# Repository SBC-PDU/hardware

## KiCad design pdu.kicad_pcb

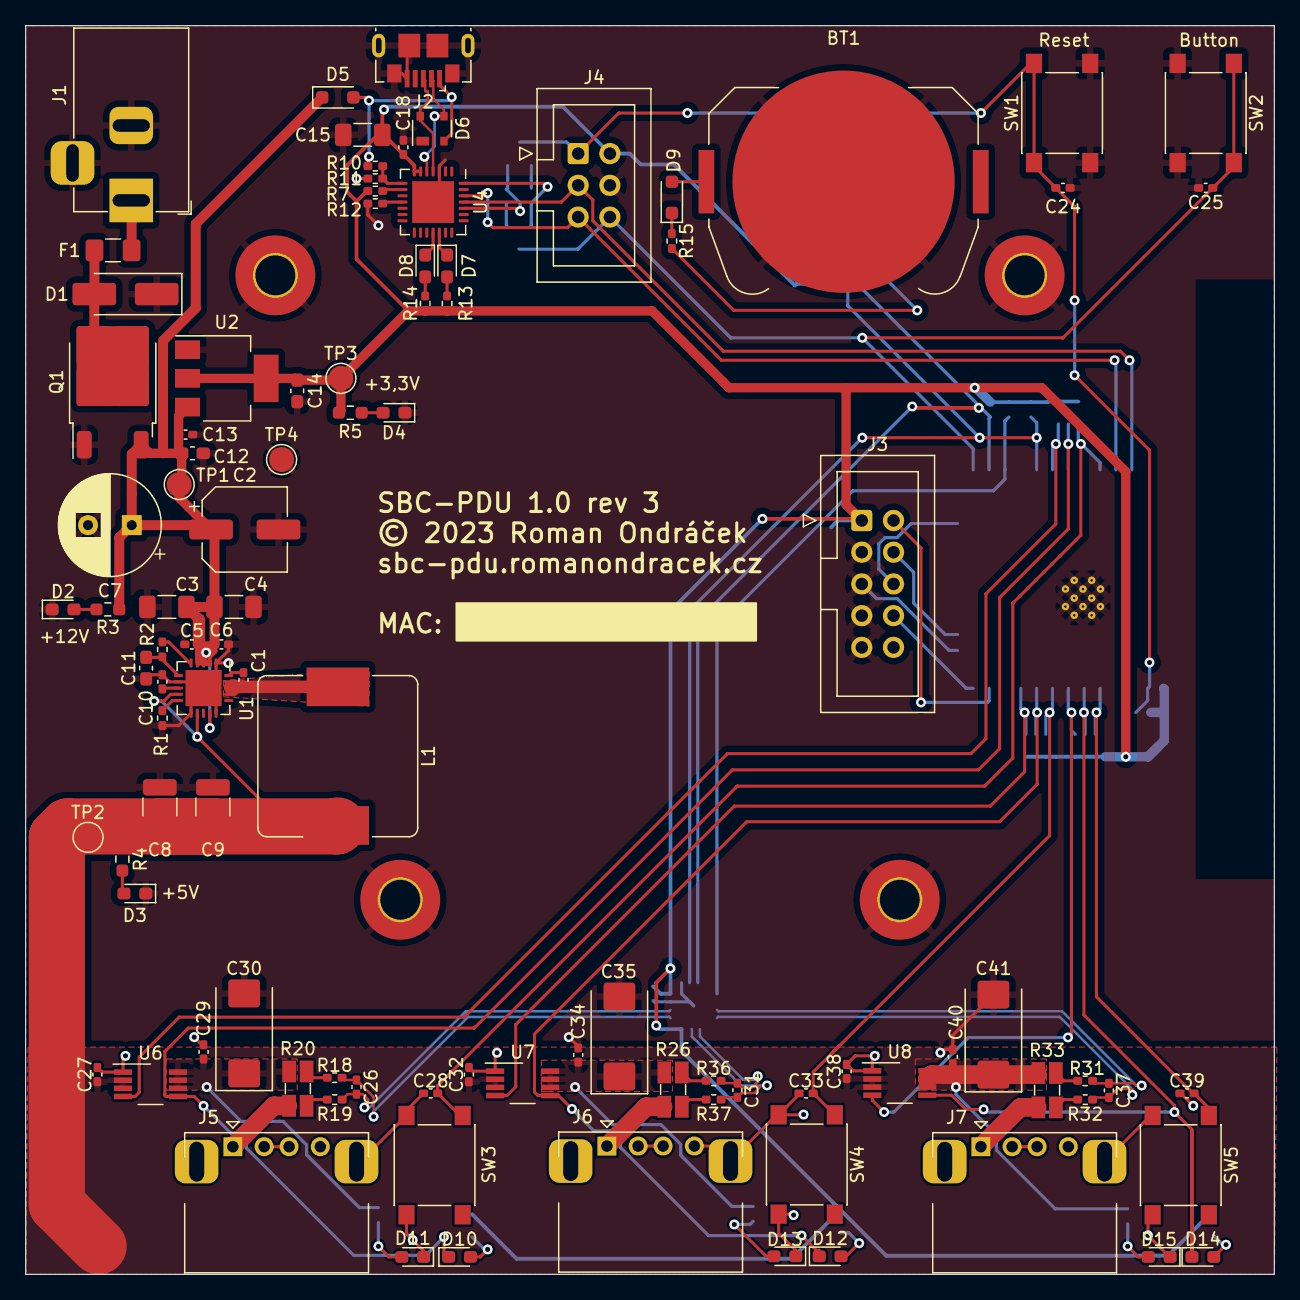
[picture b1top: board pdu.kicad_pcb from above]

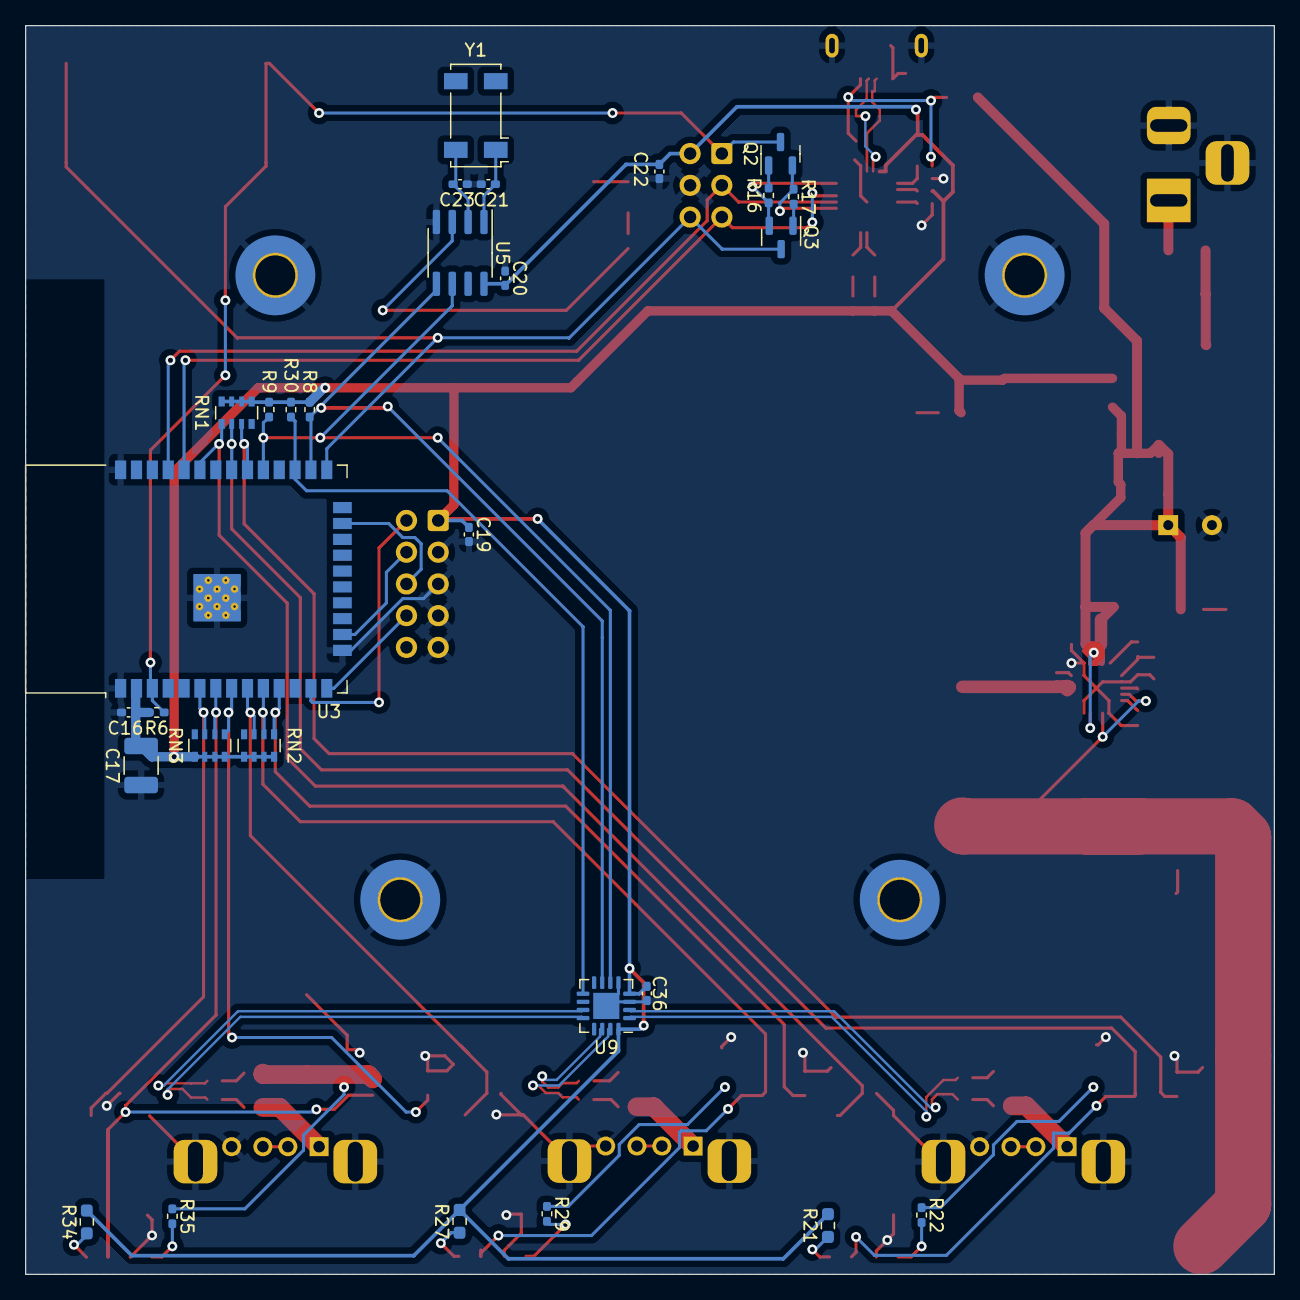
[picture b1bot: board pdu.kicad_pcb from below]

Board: 2 copper layers, 100.0 x 100.0 mm, 128 parts (29 on the bottom side), 81 nets.

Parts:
BT1: CR2032; BatteryHolder_Keystone_3034_1x20mm
C1, C13, C16, C18, C19, C20, C22, C24, C25, C27, C28, C29, C31, C32, C33, C34, C36, C37, C38, C39, C40: 100n; C_0402_1005Metric_Pad0.74x0.62mm_HandSolder
C2: 47u; CP_Elec_6.3x5.8
C3, C4, C15: 4.7u; C_1206_3216Metric_Pad1.33x1.80mm_HandSolder
C5, C6: 150p; C_0402_1005Metric_Pad0.74x0.62mm_HandSolder
C7: 470u; CP_Radial_D8.0mm_P3.50mm
C8, C9: 47u; C_1210_3225Metric_Pad1.33x2.70mm_HandSolder
C10: 5600p; C_0402_1005Metric_Pad0.74x0.62mm_HandSolder
C11: 2.2u; C_0603_1608Metric_Pad1.08x0.95mm_HandSolder
C12: 1u; C_0603_1608Metric_Pad1.08x0.95mm_HandSolder
C14: 10u; C_0603_1608Metric_Pad1.08x0.95mm_HandSolder
C17: 22u; C_1210_3225Metric_Pad1.33x2.70mm_HandSolder
C21, C23: 6.8p; C_0402_1005Metric_Pad0.74x0.62mm_HandSolder
C26: C; C_0402_1005Metric_Pad0.74x0.62mm_HandSolder
C30, C35, C41: 150u; CP_EIA-7343-31_Kemet-D_Pad2.25x2.55mm_HandSolder
D1: SMAJ12CA; D_SMA_Handsoldering
D2, D3, D8, D11, D13, D15: Green_LED; LED_0603_1608Metric_Pad1.05x0.95mm_HandSolder
D4, D7, D10, D12, D14: Amber_LED; LED_0603_1608Metric_Pad1.05x0.95mm_HandSolder
D5: BAT760-7; D_SOD-323_HandSoldering
D6: SP0503BAHTG; SOT-143
D9: BAT54WS; D_SOD-323_HandSoldering
F1: 5A; Fuse_1206_3216Metric_Pad1.42x1.75mm_HandSolder
H1, H2, H3, H4: MountingHole_Pad; MountingHole_3.2mm_M3_Pad_TopBottom
J1: DC_Jack; BarrelJack_Horizontal
J2: USB_B_Micro; USB_Micro-B_GCT_USB3076-30-A
J3: JTAG; IDC-Header_2x05_P2.54mm_Vertical
J4: UART; IDC-Header_2x03_P2.54mm_Vertical
J5, J6, J7: USB_A; USB_A_GCT_USB1125-GF-B
L1: 8.2u; L_Bourns_SRP1245A
Q1: FDD4243; TO-252-2
Q2, Q3: BC846; SOT-23
R1: 51k; R_0402_1005Metric_Pad0.72x0.64mm_HandSolder
R2, R6, R12, R15, R16, R17, R30: 10k; R_0402_1005Metric_Pad0.72x0.64mm_HandSolder
R3, R4, R5, R21, R27, R34: 430R; R_0603_1608Metric_Pad0.98x0.95mm_HandSolder
R7, R22, R29, R35: 1k; R_0402_1005Metric_Pad0.72x0.64mm_HandSolder
R8, R9: 3k3; R_0402_1005Metric_Pad0.72x0.64mm_HandSolder
R10: 22.1k; R_0402_1005Metric_Pad0.72x0.64mm_HandSolder
R11: 47.5k; R_0402_1005Metric_Pad0.72x0.64mm_HandSolder
R13, R14: 470; R_0402_1005Metric_Pad0.72x0.64mm_HandSolder
R18, R19, R31, R32, R36, R37: 10R; R_0402_1005Metric_Pad0.72x0.64mm_HandSolder
R20, R26, R33: 50m; R_Shunt_Ohmite_LVK12
RN1, RN2, RN3: 10k; R_Array_Convex_4x0603
SW1, SW2, SW3, SW4, SW5: SW_Push; SW_Push_1P1T_NO_6x6mm_H9.5mm
TP1: +12V; TestPoint_Pad_D2.0mm
TP2: +5V; TestPoint_Pad_D2.0mm
TP3: +3V3; TestPoint_Pad_D2.0mm
TP4: GND; TestPoint_Pad_D2.0mm
U1: MAX17634BATP+; TQFN-20-1EP_4x4mm_P0.5mm_EP2.9x2.9mm
U2: TLV1117LV33DCYR; SOT-223-3_TabPin2
U3: ESP32-WROOM-32D
U4: CP2102N-Axx-xQFN28; QFN-28-1EP_5x5mm_P0.5mm_EP3.35x3.35mm
U5: MCP7940N-I/SN; SOIC-8_3.9x4.9mm_P1.27mm
U6, U7, U8: TPS2000C; VSSOP-8_3.0x3.0mm_P0.65mm
U9: INA3221; Texas_RGV_S-PVQFN-N16_EP2.1x2.1mm
Y1: 32.765k; Crystal_SMD_Abracon_ABS25-4Pin_8.0x3.8mm

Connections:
+3V3: C14.1, C15.1, C16.2, C17.2, C18.1, C19.1, C20.2, C22.1, C36.2, J3.1, J4.2, R5.1, R6.1, R7.2, R8.1, R9.1, R13.1, R14.1, R21.2, R27.2, R30.1, R34.2, RN1.5 (R4.2), RN1.6 (R3.2), RN1.7 (R2.2), RN1.8 (R1.2), RN2.5 (R4.2), RN2.6 (R3.2), RN2.7 (R2.2), RN2.8 (R1.2), RN3.5 (R4.2), RN3.6 (R3.2), RN3.7 (R2.2), RN3.8 (R1.2), TP3.1, U2.2 (VO), U3.2 (VDD), U4.6 (VDD), U4.7 (VREGIN), U5.8 (VCC), U9.4 (VS), U9.16 (VPU)
+3V3_RegIn: C2.1, C3.1, C4.1, C5.1, C6.1, C7.1, C12.1, C13.1, D5.1 (K), Q1.3 (S), R3.1, TP1.1, U1.2 (IN), U1.3 (IN), U1.4 (EN/UVLO), U1.14 (IN), U2.3 (VI)
+5V: C8.1, C9.1, C27.2, C32.2, C38.2, L1.2, R4.1, TP2.1, U1.9 (FB), U1.12 (EXTVCC), U6.2 (IN), U6.3 (IN), U7.2 (IN), U7.3 (IN), U8.2 (IN), U8.3 (IN)
/ESP32/BTN: C25.1, J4.6, Q3.3 (C), SW2.1, U3.25 (IO0)
/ESP32/CRITICAL: R30.2, U3.27 (IO16), U9.9 (CRITICAL)
/ESP32/DEBUG_RX: J4.5, U3.34 (RXD0/IO3), U4.26 (TXD)
/ESP32/DEBUG_TX: J4.3, U3.35 (TXD0/IO1), U4.25 (RXD)
/ESP32/EN: C24.1, J4.1, Q2.3 (C), R6.2, SW1.1, U3.3 (EN)
/ESP32/MTCK: J3.4, U3.16 (IO13)
/ESP32/MTDI: J3.8, U3.14 (IO12)
/ESP32/MTDO: J3.6, U3.23 (IO15)
/ESP32/MTMS: J3.2, U3.13 (IO14)
/ESP32/SBC1_BTN: C28.1, RN1.1 (R1.1), SW3.1, U3.33 (IO21)
/ESP32/SBC2_BTN: C33.1, RN2.3 (R3.1), SW4.1, U3.9 (IO33)
/ESP32/SBC3_BTN: C39.1, RN3.3 (R3.1), SW5.1, U3.6 (IO34)
/ESP32/SCL: R9.2, U3.29 (IO5), U5.6 (SCL), U9.6 (SCL)
/ESP32/SDA: R8.2, U3.26 (IO4), U5.5 (SDA), U9.7 (SDA)
/ESP32/USB_D+: D6.4 (K), J2.3 (D+), U4.4 (D+)
/ESP32/USB_D-: D6.3 (K), J2.2 (D-), U4.5 (D-)
/ESP32/~DTR: Q3.2 (E), R16.1, U4.28 (~DTR)
/ESP32/~RTS: Q2.2 (E), R17.1, U4.24 (~RTS)
/ESP32/~SBC1_EN: RN1.3 (R3.1), U3.30 (IO18), U6.4 (~EN)
/ESP32/~SBC1_FLT: D10.1 (K), RN1.2 (R2.1), U3.31 (IO19), U6.5 (~FLT)
/ESP32/~SBC2_EN: RN2.1 (R1.1), U3.11 (IO26), U7.4 (~EN)
/ESP32/~SBC2_FLT: D12.1 (K), RN2.2 (R2.1), U3.10 (IO25), U7.5 (~FLT)
/ESP32/~SBC3_EN: RN3.1 (R1.1), U3.8 (IO32), U8.4 (~EN)
/ESP32/~SBC3_FLT: D14.1 (K), RN3.2 (R2.1), U3.7 (IO35), U8.5 (~FLT)
/Outputs/IN1+: C26.2, R19.1, U9.2 (IN+3)
/Outputs/IN1-: C26.1, R18.1, U9.1 (IN-3)
/Outputs/IN2+: C31.2, R37.1, U9.15 (IN+2)
/Outputs/IN2-: C31.1, R36.1, U9.14 (IN-2)
/Outputs/IN3+: C37.2, R32.1, U9.12 (IN+1)
/Outputs/IN3-: C37.1, R31.1, U9.11 (IN-1)
/Outputs/SBC1_POWER: C29.1, C30.1, R20.1, R22.1, U6.6 (OUT), U6.7 (OUT), U6.8 (OUT)
/Outputs/SBC2_POWER: C34.1, C35.1, R26.1, R29.1, U7.6 (OUT), U7.7 (OUT), U7.8 (OUT)
/Outputs/SBC3_POWER: C40.1, C41.1, R33.1, R35.1, U8.6 (OUT), U8.7 (OUT), U8.8 (OUT)
/Power/INTVCC: C11.1, R2.2, U1.6 (INTVCC)
/Power/Vin: D1.2 (A2), F1.2, Q1.2 (D)
/Power/~RESET: R2.1, U1.5 (~RESET)
GND: BT1.2 (-), C2.2, C3.2, C4.2, C5.2, C6.2, C7.2, C8.2, C9.2, C10.2, C11.2, C12.2, C13.2, C14.2, C15.2, C16.1, C17.1, C18.2, C19.2, C20.1, C21.2, C22.2, C23.2, C24.2, C25.2, C27.1, C28.2, C29.2, C30.2, C32.1, C33.2, C34.2, C35.2, C36.1, C38.1, C39.2, C40.2, C41.2, D1.1 (A1), D2.1 (K), D3.1 (K), D4.1 (K), D6.1 (A), D11.1 (K), D13.1 (K), D15.1 (K), H1.1, H2.1, H3.1, H4.1, J1.2, J1.3, J2.5 (GND), J2.6 (Shield), J3.3, J3.5, J3.7, J3.9, J4.4, J5.4 (GND), J5.5 (Shield), J6.4 (GND), J6.5 (Shield), J7.4 (GND), J7.5 (Shield), Q1.1 (G), R1.1, R11.2, R12.2, SW1.2, SW2.2, SW3.2, SW4.2, SW5.2, TP4.1, U1.1 (PGND), U1.7 (SGND), U1.11 (MODE/SYNC), U1.15 (PGND), U1.21 (SGND), U2.1 (GND), U3.1 (GND), U3.15 (GND), U3.38 (GND), U3.39 (GND), U4.3 (GND), U4.29 (GND), U5.4 (VSS), U6.1 (GND), U7.1 (GND), U8.1 (GND), U9.3 (GND), U9.5 (A0), U9.17 (EP)
unnamed: BT1.1 (+), D9.2 (A)
unnamed: C1.2, L1.1, U1.17 (LX), U1.18 (LX), U1.19 (LX)
unnamed: D2.2 (A), R3.2
unnamed: D3.2 (A), R4.2
unnamed: D4.2 (A), R5.2
unnamed: D7.2 (A), R13.2
unnamed: D7.1 (K), U4.19 (~TXT/GPIO.0)
unnamed: D8.2 (A), R14.2
unnamed: D8.1 (K), U4.18 (~RXT/GPIO.1)
unnamed: D9.1 (K), R15.1
unnamed: D10.2 (A), R21.1
unnamed: D11.2 (A), R22.2
unnamed: D12.2 (A), R27.1
unnamed: D13.2 (A), R29.2
unnamed: D14.2 (A), R34.1
unnamed: D15.2 (A), R35.2
unnamed: F1.1, J1.1
unnamed: J5.2 (D-), J5.3 (D+)
unnamed: J5.1 (VBUS), R20.4
unnamed: J6.2 (D-), J6.3 (D+)
unnamed: J6.1 (VBUS), R26.4
unnamed: J7.2 (D-), J7.3 (D+)
unnamed: J7.1 (VBUS), R33.4
unnamed: Q2.1 (B), R16.2
unnamed: Q3.1 (B), R17.2
unnamed: R18.2, R20.2
unnamed: R19.2, R20.3
unnamed: R26.2, R36.2
unnamed: R26.3, R37.2
unnamed: R31.2, R33.2
unnamed: R32.2, R33.3
unnamed: C1.1, U1.20 (BST)
unnamed: R1.2, U1.10 (RT)
unnamed: C10.1, U1.8 (SS)
unnamed: R10.1, R11.1, U4.8 (VBUS)
unnamed: R7.1, U4.9 (~RST)
unnamed: R12.1, U4.11 (~SUSPEND)
unnamed: R15.2, U5.3 (VBAT)
unnamed: C21.1, U5.1 (X1), Y1.1
unnamed: C23.1, U5.2 (X2), Y1.4
VBUS: D5.2 (A), D6.2 (K), J2.1 (VBUS), R10.2

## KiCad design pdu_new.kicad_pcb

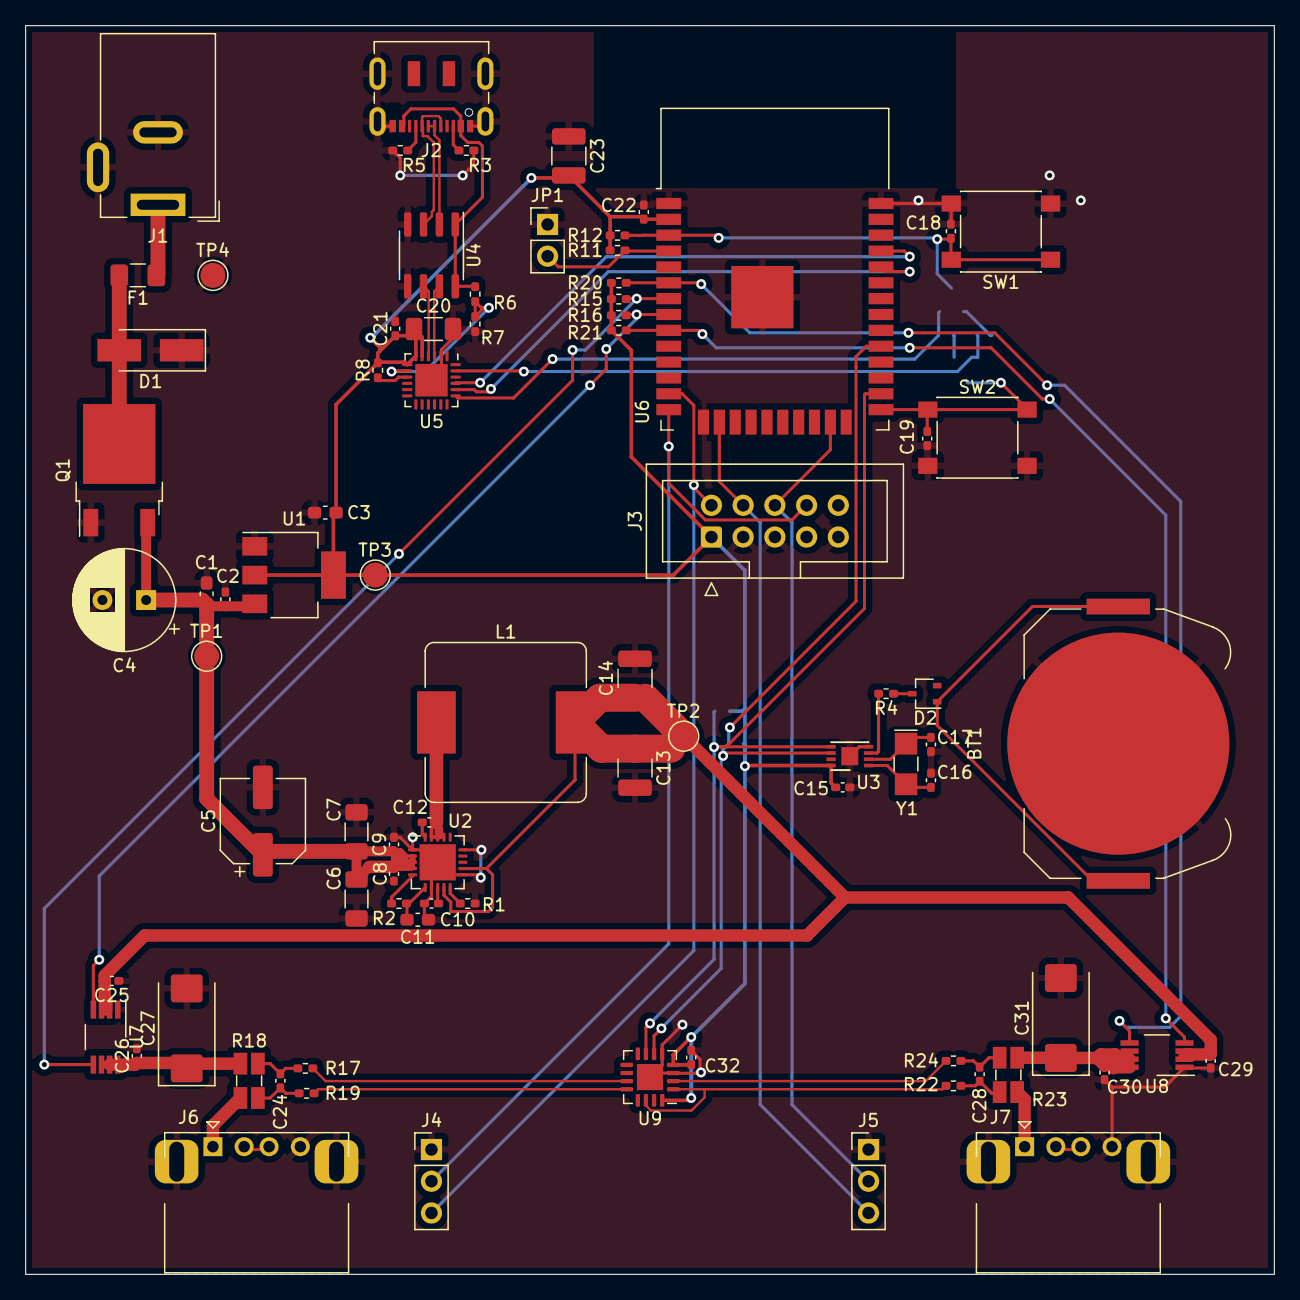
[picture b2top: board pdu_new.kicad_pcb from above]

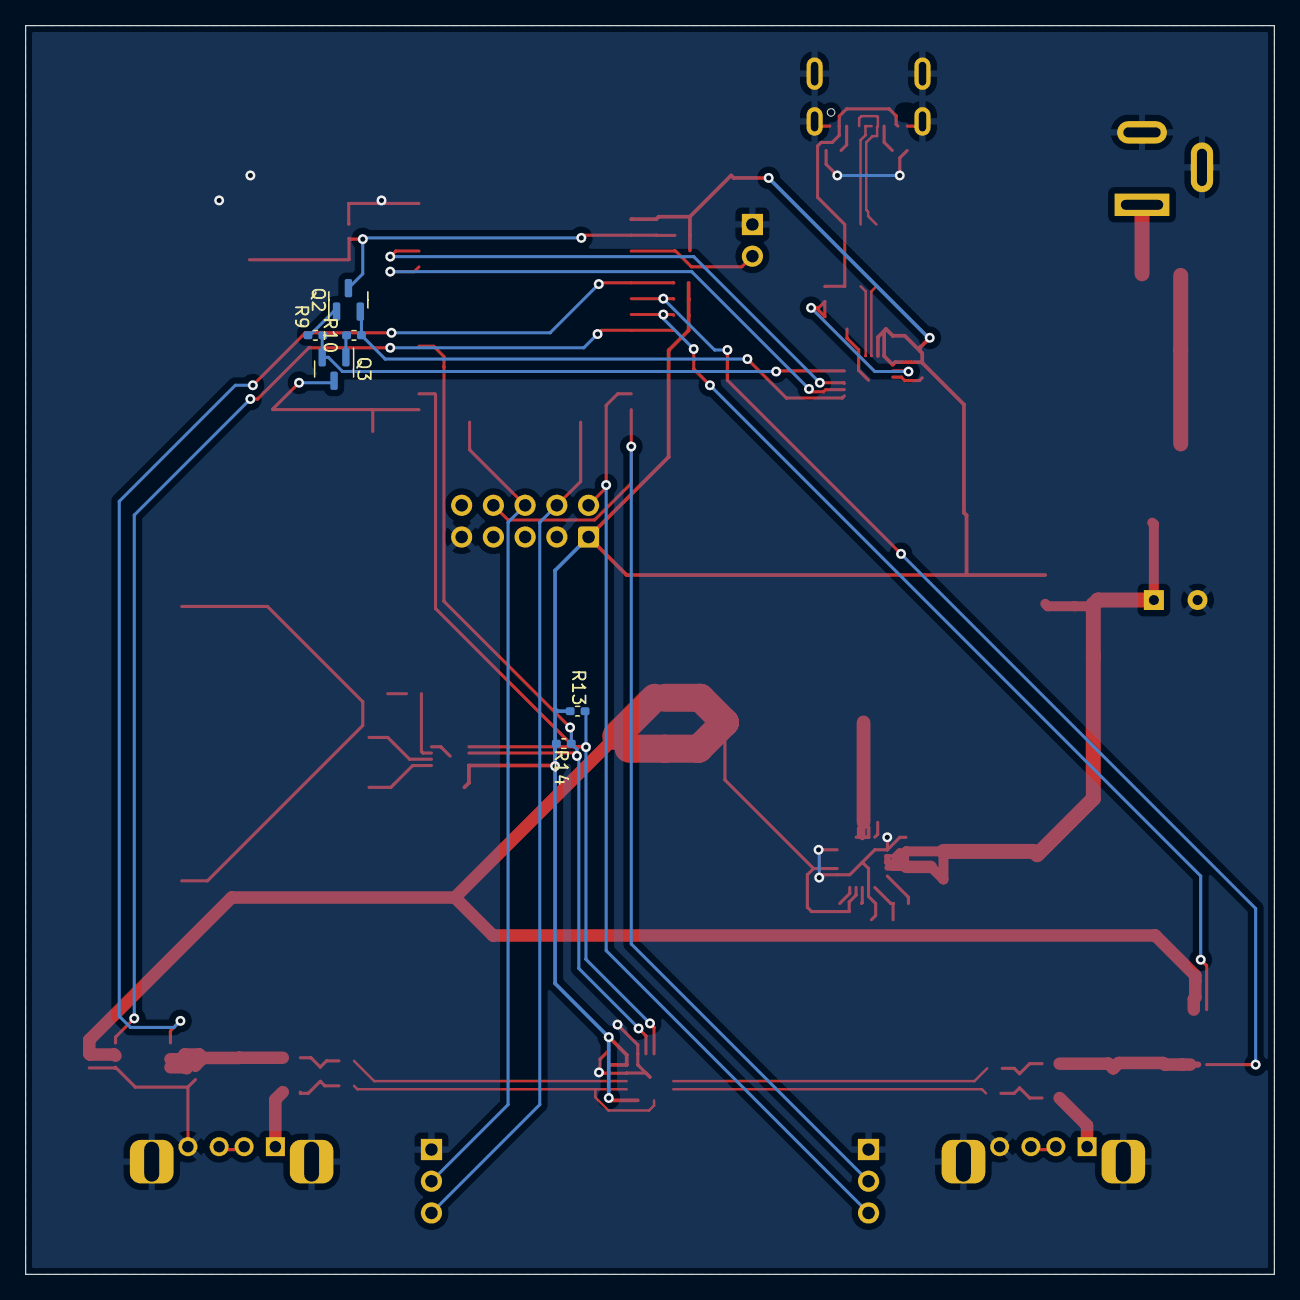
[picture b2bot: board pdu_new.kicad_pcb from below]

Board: 2 copper layers, 100.0 x 100.0 mm, 88 parts (6 on the bottom side), 59 nets.

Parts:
BT1: Battery_Cell; BatteryHolder_Keystone_3034_1x20mm
C1: 1u; C_0603_1608Metric_Pad1.08x0.95mm_HandSolder
C2, C12, C15, C18, C19, C21, C22, C25, C26, C29, C30, C32: 100n; C_0402_1005Metric_Pad0.74x0.62mm_HandSolder
C3: 10u; C_0603_1608Metric_Pad1.08x0.95mm_HandSolder
C4: 470u; CP_Radial_D8.0mm_P3.50mm
C5: 47u; CP_Elec_6.3x5.8
C6, C7, C20: 4.7u; C_1206_3216Metric_Pad1.33x1.80mm_HandSolder
C8, C9: 150p; C_0402_1005Metric_Pad0.74x0.62mm_HandSolder
C10: 5600p; C_0402_1005Metric_Pad0.74x0.62mm_HandSolder
C11: 2.2u; C_0603_1608Metric_Pad1.08x0.95mm_HandSolder
C13, C14: 47u; C_1210_3225Metric_Pad1.33x2.70mm_HandSolder
C16, C17, C24, C28: C; C_0402_1005Metric_Pad0.74x0.62mm_HandSolder
C23: 22u; C_1210_3225Metric_Pad1.33x2.70mm_HandSolder
C27, C31: 150u; CP_EIA-7343-31_Kemet-D_Pad2.25x2.55mm_HandSolder
D1: SMAJ12CA; D_SMA_Handsoldering
D2: BAT54W; SOT-323_SC-70
F1: 5A; Fuse_1206_3216Metric_Pad1.42x1.75mm_HandSolder
J1: Wuerth_694108301002; BarrelJack_Wuerth_6941xx301002
J2: USB_C_Receptacle_USB2.0; USB_C_Receptacle_JAE_DX07S016JA1R1500
J3: Conn_ARM_JTAG_SWD_10; IDC-Header_2x05_P2.54mm_Vertical
J4: SBC1_UART; PinHeader_1x03_P2.54mm_Vertical
J5: SBC2_UART; PinHeader_1x03_P2.54mm_Vertical
J6, J7: USB_A; USB_A_GCT_USB1125-GF-B
JP1: JTAG_EN; PinHeader_1x02_P2.54mm_Vertical
L1: 8.2uH; L_Bourns_SRP1245A
Q1: FDD4243; TO-252-2
Q2, Q3: BC846; SOT-23
R1: 51k; R_0402_1005Metric_Pad0.72x0.64mm_HandSolder
R2, R4, R9, R10, R11, R12, R15, R16, R20, R21: 10k; R_0402_1005Metric_Pad0.72x0.64mm_HandSolder
R3, R5: 5.1k; R_0402_1005Metric_Pad0.72x0.64mm_HandSolder
R6: 22.1k; R_0402_1005Metric_Pad0.72x0.64mm_HandSolder
R7: 47.5k; R_0402_1005Metric_Pad0.72x0.64mm_HandSolder
R8: 1k; R_0402_1005Metric_Pad0.72x0.64mm_HandSolder
R13, R14: 3k3; R_0402_1005Metric_Pad0.72x0.64mm_HandSolder
R17, R19, R22, R24: 10R; R_0402_1005Metric_Pad0.72x0.64mm_HandSolder
R18, R23: R_Shunt; R_Shunt_Ohmite_LVK12
SW1, SW2: SW_Push; SW_Push_1P1T_NO_6x6mm_H9.5mm
TP1: +12V; TestPoint_Pad_D2.0mm
TP2: +5V; TestPoint_Pad_D2.0mm
TP3: +3V3; TestPoint_Pad_D2.0mm
TP4: GND; TestPoint_Pad_D2.0mm
U1: LD1117S33TR_SOT223; SOT-223-3_TabPin2
U2: MAX17634BATP+; TQFN-20-1EP_4x4mm_P0.5mm_EP2.9x2.9mm
U3: MCP7940N-xMNY; DFN-8-1EP_3x2mm_P0.5mm_EP1.36x1.46mm
U4: USB6B1; SOIC-8_3.9x4.9mm_P1.27mm
U5: CP2102N-Axx-xQFN24; QFN-24-1EP_4x4mm_P0.5mm_EP2.6x2.6mm
U6: ESP32-WROOM-32D; ESP32-WROOM-32
U7, U8: TPS2000C; VSSOP-8_3.0x3.0mm_P0.65mm
U9: INA3221; Texas_RGV_S-PVQFN-N16_EP2.1x2.1mm
Y1: 32.768 kHz; Crystal_SMD_G8-2Pin_3.2x1.5mm_HandSoldering

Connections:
+3V3: C3.1, C15.2, C20.1, C21.1, C22.2, C23.2, C32.2, J3.1 (VTref), R8.2, R11.1, R12.1, R13.1, R14.1, R15.1, R16.2, R20.1, R21.2, TP3.1, U1.2 (VO), U3.8 (VCC), U5.5 (VIO), U5.6 (VDD), U5.7 (VREGIN), U6.2 (VDD), U9.4 (VS), U9.16 (VPU)
+5V: C13.1, C14.1, C25.2, C29.2, L1.2, TP2.1, U2.9 (FB), U2.12 (EXTVCC), U7.2 (IN), U7.3 (IN), U8.2 (IN), U8.3 (IN)
+12V: C1.1, C2.1, C4.1, C5.1, C6.1, C7.1, C8.1, C9.1, Q1.3 (S), TP1.1, U1.3 (VI), U2.2 (IN), U2.3 (IN), U2.4 (EN/UVLO), U2.14 (IN)
/ESP32/BTN: C19.1, Q3.3 (C), SW2.1, U6.25 (IO0)
/ESP32/D+: U4.7 (I/O1), U5.3 (D+)
/ESP32/D-: U4.6 (I/O2), U5.4 (D-)
/ESP32/DATA+: J2.A6 (D+), J2.B6 (D+), U4.2 (I/O1)
/ESP32/DATA-: J2.A7 (D-), J2.B7 (D-), U4.3 (I/O2)
/ESP32/DEBUG_RX: U5.20 (RXD), U6.34 (RXD0/IO3)
/ESP32/DEBUG_TX: U5.21 (TXD), U6.35 (TXD0/IO1)
/ESP32/EN: C18.1, Q2.3 (C), R12.2, SW1.1, U6.3 (EN)
/ESP32/MTCK/SBC2_TX: J3.4 (SWDCLK/TCK), J5.3, U6.16 (IO13)
/ESP32/MTDI/SBC1_RX: J3.8 (NC/TDI), J4.2, U6.14 (IO12)
/ESP32/MTDO/SBC2_RX: J3.6 (SWO/TDO), J5.2, U6.23 (IO15)
/ESP32/MTMS/SBC1_RX: J3.2 (SWDIO/TMS), J4.3, U6.13 (IO14)
/ESP32/SCL: R14.2, U3.6 (SCL), U6.29 (IO5), U9.6 (SCL)
/ESP32/SDA: R13.2, U3.5 (SDA), U6.26 (IO4), U9.7 (SDA)
/ESP32/~DTR: Q3.2 (E), R9.1, U5.23 (~DTR)
/ESP32/~JTAG_EN: JP1.2 (B), R11.2, U6.4 (SENSOR_VP)
/ESP32/~RTS: Q2.2 (E), R10.1, U5.19 (~RTS)
/ESP32/~SBC1_EN: R16.1, U6.8 (IO32), U7.4 (~EN)
/ESP32/~SBC1_FLT: R15.2, U6.7 (IO35), U7.5 (~FLT)
/ESP32/~SBC2_EN: R21.1, U6.9 (IO33), U8.4 (~EN)
/ESP32/~SBC2_FLT: R20.2, U6.6 (IO34), U8.5 (~FLT)
/Outputs/IN+1: R19.2, U9.12 (IN+1)
/Outputs/IN+2: R24.2, U9.2 (IN+3)
/Outputs/IN-1: R17.1, U9.11 (IN-1)
/Outputs/IN-2: R22.1, U9.1 (IN-3), U9.14 (IN-2)
/Outputs/USB1_PWR: C26.1, C27.1, R18.4, U7.6 (OUT), U7.7 (OUT), U7.8 (OUT)
/Outputs/USB2_PWR: C30.1, C31.1, R23.4, U8.6 (OUT), U8.7 (OUT), U8.8 (OUT)
/Power/INTVCC: C11.1, R2.2, U2.6 (INTVCC)
/Power/~RESET: R2.1, U2.5 (~RESET)
GND: BT1.2 (-), C1.2, C2.2, C3.2, C4.2, C5.2, C6.2, C7.2, C8.2, C9.2, C10.2, C11.2, C13.2, C14.2, C15.1, C16.2, C17.2, C18.2, C19.2, C20.2, C21.2, C22.1, C23.1, C25.1, C26.2, C27.2, C29.1, C30.2, C31.2, C32.1, D1.1 (A1), J1.2, J1.3, J2.A1 (GND), J2.A12 (GND), J2.B1 (GND), J2.B12 (GND), J2.S1 (SHIELD), J3.3 (GND), J3.5 (GND), J3.9 (GNDDetect), J4.1, J5.1, J6.4 (GND), J6.5 (Shield), J7.4 (GND), J7.5 (Shield), JP1.1 (A), Q1.1 (G), R1.1, R3.2, R5.2, R7.1, SW1.2, SW2.2, TP4.1, U1.1 (GND), U2.1 (PGND), U2.7 (SGND), U2.11 (MODE/SYNC), U2.15 (PGND), U2.21 (SGND), U3.4 (VSS), U3.9 (EP), U4.4 (GND), U4.5 (GND), U5.2 (GND), U5.25 (GND), U6.1 (GND), U6.15 (GND), U6.38 (GND), U6.39 (GND), U7.1 (GND), U8.1 (GND), U9.3 (GND), U9.5 (A0), U9.17 (EP)
unnamed: BT1.1 (+), D2.1 (A)
unnamed: C10.1, U2.8 (SS)
unnamed: C12.1, U2.20 (BST)
unnamed: C12.2, L1.1, U2.17 (LX), U2.18 (LX), U2.19 (LX)
unnamed: C16.1, U3.1 (X1), Y1.2
unnamed: C17.1, U3.2 (X2), Y1.1
unnamed: C24.1, R17.2, R18.2
unnamed: C24.2, R18.3, R19.1
unnamed: C28.1, R22.2, R23.2
unnamed: C28.2, R23.3, R24.1
unnamed: D1.2 (A2), F1.2, Q1.2 (D)
unnamed: D2.3 (K), R4.1
unnamed: F1.1, J1.1
unnamed: J2.A5 (CC1), R3.1
unnamed: J2.B5 (CC2), R5.1
unnamed: J6.1 (VBUS), R18.1
unnamed: J6.2 (D-), J6.3 (D+)
unnamed: J7.1 (VBUS), R23.1
unnamed: J7.2 (D-), J7.3 (D+)
unnamed: Q2.1 (B), R9.2
unnamed: Q3.1 (B), R10.2
unnamed: R1.2, U2.10 (RT)
unnamed: R4.2, U3.3 (VBAT)
unnamed: R6.1, R7.2, U5.8 (VBUS)
unnamed: R8.1, U5.9 (~RST)
VBUS: J2.A4 (VBUS), J2.A9 (VBUS), J2.B4 (VBUS), J2.B9 (VBUS), R6.2, U4.1 (VBUS), U4.8 (VBUS)

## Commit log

2023-04-17 Second revision
2023-05-03 Third revision
2023-05-09 Fix third revision

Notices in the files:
pdu.kicad_pcb:
© 2023 Roman Ondráček
